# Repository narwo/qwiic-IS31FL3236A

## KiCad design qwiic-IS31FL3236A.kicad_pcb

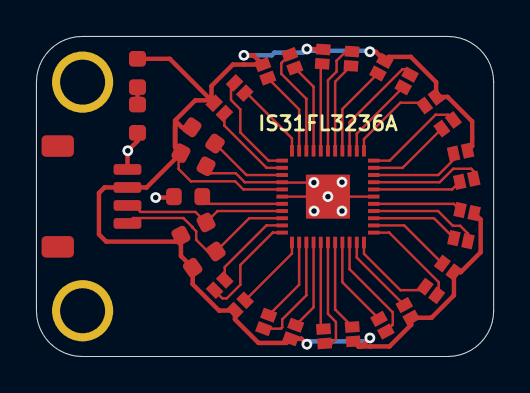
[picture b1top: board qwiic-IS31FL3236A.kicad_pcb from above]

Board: 2 copper layers, 25.4 x 17.8 mm, 23 parts (0 on the bottom side), 43 nets.

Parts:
C1: 100nF; C_0603
D1: GREEN; LED_0603
D2, D3, D4, D5, D6, D7, D8, D9, D10, D11, D12, D13: RBAG; LED_2020_RGBA
H1, H3: MountingHole; MountingHole_M2.5
J2: Qwiic; JST_SH_1x04_H
R1, R4, R5: 10k; R_0603
R2: 3.3k; R_0603
R3: 100k; R_0603
U1: IS31FL3236A; QFN_40_5x5_0.8_Thermal

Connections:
+3V3: C1.1, D2.3, D3.3, D4.3, D5.3, D6.3, D7.3, D8.3, D9.3, D10.3, D11.3, D12.3, D13.3, J2.2, R1.1, R3.2, R4.1, R5.1, U1.38
/P01: D7.1, U1.43
/P02: D7.4, U1.44
/P03: D7.2, U1.1
/P04: D2.1, U1.2
/P05: D2.4, U1.3
/P06: D2.2, U1.4
/P07: D3.1, U1.5
/P08: D3.4, U1.6
/P09: D3.2, U1.7
/P10: D4.1, U1.8
/P11: D4.4, U1.9
/P12: D4.2, U1.10
/P13: D5.1, U1.11
/P14: D5.4, U1.12
/P15: D5.2, U1.13
/P16: D6.1, U1.14
/P17: D6.4, U1.15
/P18: D6.2, U1.16
/P19: D8.1, U1.18
/P20: D8.4, U1.19
/P21: D8.2, U1.20
/P22: D9.1, U1.21
/P23: D9.4, U1.22
/P24: D9.2, U1.23
/P25: D10.1, U1.24
/P26: D10.4, U1.25
/P27: D10.2, U1.26
/P28: D11.1, U1.27
/P29: D11.4, U1.28
/P30: D11.2, U1.29
/P31: D12.1, U1.30
/P32: D12.4, U1.31
/P33: D12.2, U1.32
/P34: D13.1, U1.33
/P35: D13.4, U1.34
/P36: D13.2, U1.35
/SCL: J2.4, R5.2, U1.42
/SDA: J2.3, R4.2, U1.41
GND: C1.2, D1.1, J2.1, R2.1, U1.17, U1.37, U1.39, U1.45
unnamed: D1.2, R1.2
unnamed: R2.2, U1.40
unnamed: R3.1, U1.36
